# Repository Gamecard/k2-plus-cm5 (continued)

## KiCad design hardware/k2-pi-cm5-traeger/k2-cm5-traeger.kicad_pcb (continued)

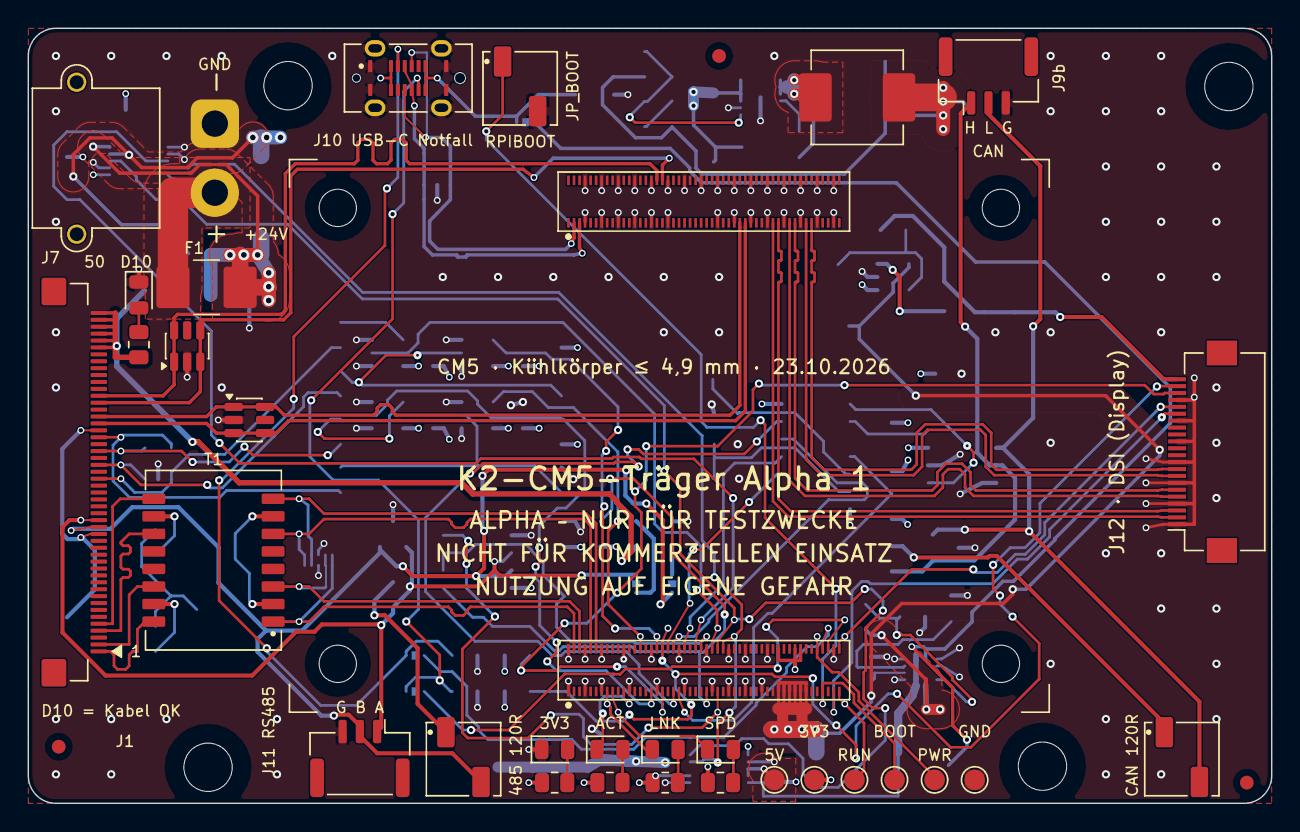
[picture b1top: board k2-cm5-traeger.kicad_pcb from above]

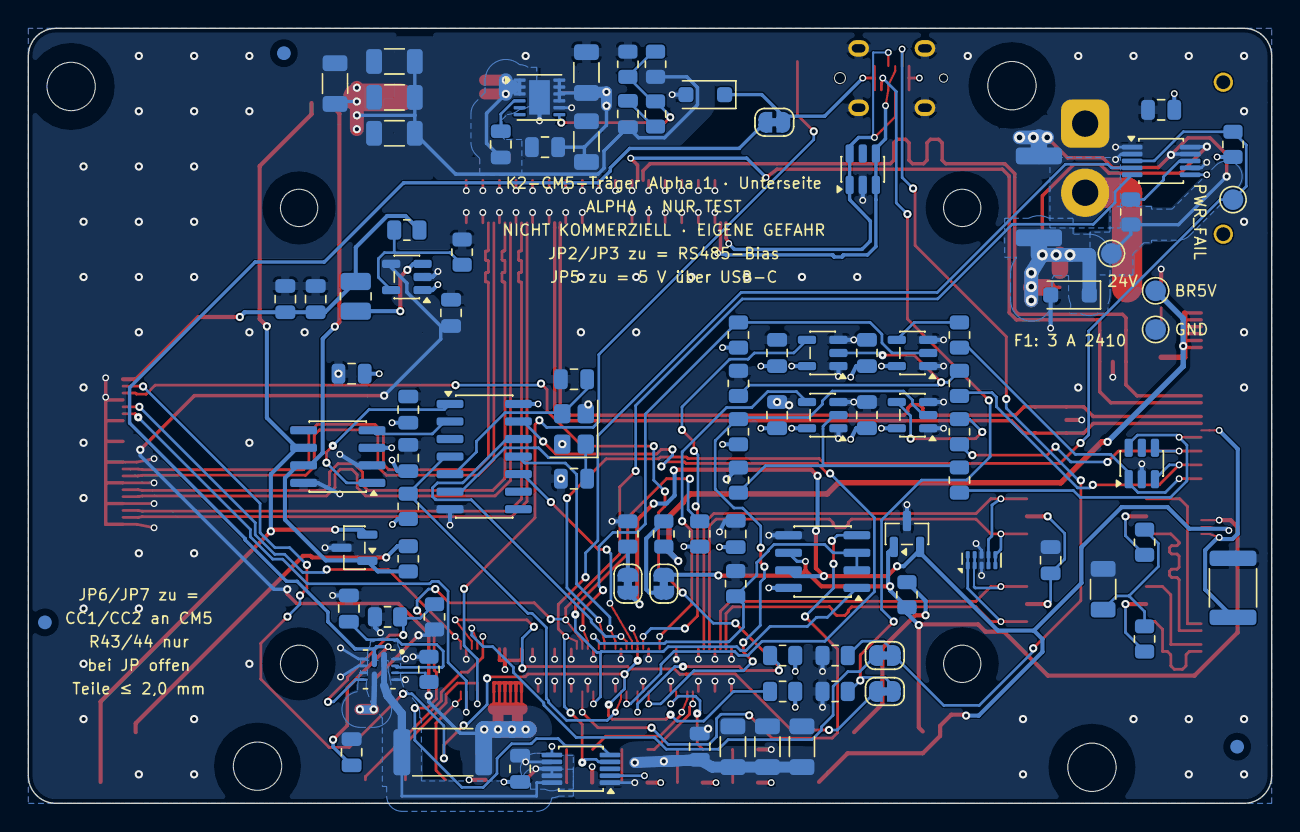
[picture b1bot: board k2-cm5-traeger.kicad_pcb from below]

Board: 4 copper layers, 90.0 x 56.1 mm, 137 parts (99 on the bottom side), 101 nets.

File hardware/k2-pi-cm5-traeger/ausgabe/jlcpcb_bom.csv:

Comment,Designator,Footprint,LCSC Part #,MPN,Manufacturer,Quantity,Notes
22p,"C1,C2",C_0805_2012Metric,C1804,CL21C220JBANNNC,Samsung Electro-Mechanics,2,"Basic; UNTERSEITE: C1,C2"
100n,"C3,C5,C6,C7,C11,C12,C22,C25,C27,C30,C31,C32,C33",C_0805_2012Metric,C49678,CC0805KRX7R9BB104,YAGEO,13,"Basic; UNTERSEITE: C3,C5,C6,C7,C11,C12,C22,C25,C27,C30,C31,C32,C33"
10u,"C4,C18,C34",C_0805_2012Metric,C15850,CL21A106KAYNNNE,Samsung Electro-Mechanics,3,"Basic; UNTERSEITE: C4,C18,C34"
22n,C8,C_0805_2012Metric,C107147,CC0805KRX7R9BB223,YAGEO,1,Extended; UNTERSEITE: C8
10u50,"C9,C10",C_1206_3216Metric,C13585,CL31A106KBHNNNE,Samsung Electro-Mechanics,2,"Basic; UNTERSEITE: C9,C10"
33p,C13,C_0805_2012Metric,C107115,CC0805JRNPO9BN330,YAGEO,1,Extended; UNTERSEITE: C13
22u25,"C14,C15,C16,C17,C19,C20,C21",C_1206_3216Metric,C12891,CL31A226KAHNNNE,Samsung Electro-Mechanics,7,"Basic; UNTERSEITE: C14,C15,C16,C17,C19,C20,C21"
1n2kV,C28,C_1206_3216Metric,C9196,1206B102K202NT,FH (Guangdong Fenghua),1,Basic; UNTERSEITE: C28
22u6,"C35,C36",C_0805_2012Metric,C5674,CL21A226MQQNNNE,Samsung Electro-Mechanics,2,"Extended; UNTERSEITE: C35,C36"
USBLC6-2SC6,"D1,D2,D3",SOT-23-6,C7519,USBLC6-2SC6,STMicroelectronics,3,Extended; Pin 1/Drehung in der JLC-Vorschau prüfen; UNTERSEITE: D3
SRV05-4,D4,SOT-23-6,C5240367,SRV05-4,TWGMC,1,Extended; Pin 1/Drehung in der JLC-Vorschau prüfen; UNTERSEITE: D4
SM712,D5,SOT-23,C502564,SM712,MDD (Microdiode),1,Extended; Pin 1/Drehung in der JLC-Vorschau prüfen; UNTERSEITE: D5
NUP2105L,D6,SOT-23,C14486,NUP2105LT1G,onsemi,1,Extended; Pin 1/Drehung in der JLC-Vorschau prüfen; UNTERSEITE: D6
TPD4E05U06,D7,USON-10_2.5x1.0mm_P0.5mm,C138714,TPD4E05U06DQAR,Texas Instruments,1,Extended; Pin 1/Drehung in der JLC-Vorschau prüfen; UNTERSEITE: D7
SMFJ28A,D8,D_SOD-123F,C5439963,SMFJ28A,BORN,1,Extended; Pin 1/Drehung in der JLC-Vorschau prüfen; UNTERSEITE: D8
LED 0805 rot,D10,LED_0805_2012Metric,C84256,NCD0805R1,Foshan NationStar,1,Basic; Pin 1/Drehung in der JLC-Vorschau prüfen
LED 0805 grün,"D11,D12,D13",LED_0805_2012Metric,C2297,KT-0805G,Hubei KENTO,3,Basic; Pin 1/Drehung in der JLC-Vorschau prüfen
LED 0805 gelb,D14,LED_0805_2012Metric,C2296,KT-0805Y,Hubei KENTO,1,Basic; Pin 1/Drehung in der JLC-Vorschau prüfen
SMF5.0A,D15,D_SOD-123F,C193402,SMF5.0A,MDD (Microdiode),1,Extended; Pin 1/Drehung in der JLC-Vorschau prüfen; UNTERSEITE: D15
3A tauschbar,F1,Sicherungshalter_Littelfuse_157_Nano2_2410,C187520,0157003.DR,Littelfuse,1,Extended
"PTC 0,5A 30V",F3,Fuse_1812_4532Metric,C12559,SMD1812P050TF/30,PTTC (Polytronics),1,Extended; UNTERSEITE: F3
FPC-05FB-50PH20,J1,FFC_XUNPU_FPC-05FB-50PH20_1x50_P0.5mm_Horizontal,C2856838,FPC-05FB-50PH20,XUNPU,1,Extended; Pin 1/Drehung in der JLC-Vorschau prüfen
DF40C-100DS-0.4V(51),"J2A,J2B",CM5_Modul_2xDF40C-100DS-0.4V51_1.5mm,C597931,DF40C-100DS-0.4V(51),Hirose (HRS),2,Extended; Pin 1/Drehung in der JLC-Vorschau prüfen
XT30 24V,J7,AMASS_XT30PW-M_1x02_P2.50mm_Horizontal,C431092,XT30PW-M30.G.Y,Changzhou Amass,1,"Extended; Pin 1/Drehung in der JLC-Vorschau prüfen; THT – Handlöten (hand soldering), Stecköffnung zeigt über Kante A nach außen"
CAN H/L/GND,J9b,JST_GH_BM03B-GHS-TBT_1x03-1MP_P1.25mm_Vertical,C161691,BM03B-GHS-TBT(LF)(SN),JST,1,Extended; Pin 1/Drehung in der JLC-Vorschau prüfen
USB-C stehend,J10,USB_C_Buchse_stehend_16P_TYPE-C-16P-LTH6.8,C5187468,TYPE-C 16P LTH6.8,SHOU HAN,1,Extended; Pin 1/Drehung in der JLC-Vorschau prüfen
RS485 A/B/GND,J11,JST_GH_BM03B-GHS-TBT_1x03-1MP_P1.25mm_Vertical,C161691,BM03B-GHS-TBT(LF)(SN),JST,1,Extended; Pin 1/Drehung in der JLC-Vorschau prüfen
DSI 22-pol.,J12,Hirose_FH12-22S-0.5SH_1x22-1MP_P0.50mm_Horizontal,C597981,FH12-22S-0.5SH(55),Hirose (HRS),1,Extended; Pin 1/Drehung in der JLC-Vorschau prüfen
485 120R,JP_485_TERM,Stiftleiste_1x2_P2.54mm_SMD_stehend,C41417359,HX PZ2.54-1x2P TP-YQ,HX (Hanxia),1,Extended; Pin 1/Drehung in der JLC-Vorschau prüfen
RPIBOOT,JP_BOOT,Stiftleiste_1x2_P2.54mm_SMD_stehend,C41417359,HX PZ2.54-1x2P TP-YQ,HX (Hanxia),1,Extended; Pin 1/Drehung in der JLC-Vorschau prüfen
CAN 120R,JP_CAN_TERM,Stiftleiste_1x2_P2.54mm_SMD_stehend,C41417359,HX PZ2.54-1x2P TP-YQ,HX (Hanxia),1,Extended; Pin 1/Drehung in der JLC-Vorschau prüfen
"4,7µH",L1,L_Changjiang_FXL0630,C167220,FXL0630-4R7-M,cjiang (Changjiang Microelectronics),1,Extended
"2,2µH",L2,L_1008_2520Metric,C97031,WPN252010H2R2MT,lt. LCSC C97031,1,Extended; UNTERSEITE: L2
1k,"R1,R2,R3,R4,R15,R16,R20,R28,R41,R42",R_0805_2012Metric,C17513,0805W8F1001T5E,UNI-ROYAL,10,"Basic; UNTERSEITE: R1,R2,R3,R4,R15,R16,R20,R28"
100k,"R9,R10,R45",R_0805_2012Metric,C149504,0805W8F1003T5E,UNI-ROYAL,3,"Basic; UNTERSEITE: R9,R10,R45"
10k,"R11,R12,R13,R14,R18,R30,R50",R_0805_2012Metric,C17414,0805W8F1002T5E,UNI-ROYAL,7,"Basic; UNTERSEITE: R11,R12,R13,R14,R18,R30,R50"
120,"R17,R19",R_0805_2012Metric,C17437,0805W8F1200T5E,UNI-ROYAL,2,"Basic; UNTERSEITE: R17,R19"
5m,R23,R_2512_6332Metric,C185817,RLM25FEER005,Ralec,1,Extended; UNTERSEITE: R23
10m,R24,R_2512_6332Metric,C2962784,HoLLR2512-2W-10mR-1%,Hongtai,1,Extended; UNTERSEITE: R24
105k,R26,R_0805_2012Metric,C17410,0805W8F1053T5E,UNI-ROYAL,1,Extended; UNTERSEITE: R26
19k1,R27,R_0805_2012Metric,C17508,0805W8F1912T5E,UNI-ROYAL,1,Extended; UNTERSEITE: R27
33k,R29,R_0805_2012Metric,C17633,0805W8F3302T5E,UNI-ROYAL,1,Basic; UNTERSEITE: R29
18k7,R31,R_0805_2012Metric,C17499,0805W8F1872T5E,UNI-ROYAL,1,Extended; UNTERSEITE: R31
75,"R36,R37",R_0805_2012Metric,C17820,0805W8F750JT5E,UNI-ROYAL,2,"Extended; UNTERSEITE: R36,R37"
2k2,"R38,R48,R49",R_0805_2012Metric,C17520,0805W8F2201T5E,UNI-ROYAL,3,"Basic; UNTERSEITE: R48,R49"
470,"R39,R40",R_0805_2012Metric,C17710,0805W8F4700T5E,UNI-ROYAL,2,Basic
22k,R46,R_0805_2012Metric,C17560,0805W8F2202T5E,UNI-ROYAL,1,Basic; UNTERSEITE: R46
H1102NLT,T1,Uebertrager_SMD_H1102NLT_12.7x7.1mm,C18584,H1102NLT,Pulse Electronics,1,Extended; Pin 1/Drehung in der JLC-Vorschau prüfen
MCP2518FD,U1,SOIC-14_3.9x8.7mm_P1.27mm,C626759,MCP2518FDT-H/SL,Microchip,1,Extended; Pin 1/Drehung in der JLC-Vorschau prüfen; UNTERSEITE: U1
SN65HVD230,U2,SOIC-8_3.9x4.9mm_P1.27mm,C12084,SN65HVD230DR,Texas Instruments,1,Extended; Pin 1/Drehung in der JLC-Vorschau prüfen; UNTERSEITE: U2
THVD1450DR,U3,SOIC-8_3.9x4.9mm_P1.27mm,C2671361,THVD1450DR,Texas Instruments,1,Extended; Pin 1/Drehung in der JLC-Vorschau prüfen; UNTERSEITE: U3
INA226,"U4,U5",MSOP-10_3x3mm_P0.5mm,C49851,INA226AIDGSR,Texas Instruments,2,"Extended; Pin 1/Drehung in der JLC-Vorschau prüfen; UNTERSEITE: U4,U5"
LMR51450SDRRR,U7,WSON-12-1EP_3x3mm_P0.5mm_EP1.5x2.5mm,C6890985,LMR51450SDRRR,Texas Instruments,1,Extended; Pin 1/Drehung in der JLC-Vorschau prüfen; UNTERSEITE: U7
TPS2121RUXR,U8,Texas_RUX_VQFN-HR-12_2x2.5mm_P0.5mm,C485916,TPS2121RUXR,Texas Instruments,1,Extended; Pin 1/Drehung in der JLC-Vorschau prüfen; UNTERSEITE: U8
SN74LVC1G125,"U10,U11,U12,U13",SOT-23-5,C23654,SN74LVC1G125DBVR,Texas Instruments,4,"Extended; Pin 1/Drehung in der JLC-Vorschau prüfen; UNTERSEITE: U10,U11,U12,U13"
TLV62569DBVR,U14,SOT-23-5,C141836,TLV62569DBVR,Texas Instruments,1,Extended; Pin 1/Drehung in der JLC-Vorschau prüfen; UNTERSEITE: U14
40 MHz,Y1,Crystal_SMD_3225-4Pin_3.2x2.5mm,C426990,S3240000151040,JGHC,1,Extended; Pin 1/Drehung in der JLC-Vorschau prüfen; UNTERSEITE: Y1

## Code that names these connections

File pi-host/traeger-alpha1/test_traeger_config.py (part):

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    keine GPIO-Doppelbelegung (Overlays + Stromausfall-Dienst); nur unbeschaltete Pins
    dürfen nebenbei belegt werden (GPIO16 CTS, GPIO7 CE1).
 3. GPIO6 und GPIO26 (früher Toolhead-eFuse) werden nirgends verwendet; im Schaltplan frei.
 4. CAN: spi0-0 = CAN_CS an GPIO8, interrupt=25 = CAN_INT, oscillator = Quarz Y1.
 5. RS485: THVD1450 DE und ~RE an RS485_DE = GPIO17 = UART0-RTS (uart0-pi5,rs485).
 6. INA226-Overlay: Adressen aus A1/A0, Shunts aus Generator + Stückliste, ALERT 0x40 ->
    PWR_FAIL_N -> GPIO27 = k2_stromausfall-Standard; kein 0x44 mehr.
 7. DSI: vc4-kms-dsi-7inch (DSI1) <-> MIPI1-Netze, I2C ID_SD/ID_SC = GPIO0/1.
 8. Klipper-Ausschnitte: ttyAMA<n> passt zu uart<n>-pi5; Main = UART4, Düse = UART2
    (Generator), RS485 = ttyAMA0 mit rs485_de: kernel (von k2_485.py akzeptiert),
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    1: ("DSI_SCL", "i2c_csi_dsi SCL (Display)", "vc4-kms-dsi-7inch"),
    2: ("I2C1_SDA", "I2C1 SDA (INA226)", "i2c_arm"),
    3: ("I2C1_SCL", "I2C1 SCL (INA226)", "i2c_arm"),
    4: ("UART2_TX", "UART2 TX (Düsen-MCU)", "uart2-pi5"),
    5: ("UART2_RX", "UART2 RX (Düsen-MCU)", "uart2-pi5"),
    7: (None, "SPI0 CE1 (unbenutzt, nicht beschaltet)", "mcp251xfd"),
    8: ("CAN_CS", "SPI0 CE0 (MCP2518FD)", "mcp251xfd"),
    9: ("CAN_MISO", "SPI0 MISO", "mcp251xfd"),
    10: ("CAN_MOSI", "SPI0 MOSI", "mcp251xfd"),
    11: ("CAN_SCK", "SPI0 SCLK", "mcp251xfd"),
    12: ("UART4_TX", "UART4 TX (Main-MCU)", "uart4-pi5"),
    13: ("UART4_RX", "UART4 RX (Main-MCU)", "uart4-pi5"),
    14: ("UART0_TX", "UART0 TX (RS485 DI)", "uart0-pi5"),
    15: ("UART0_RX", "UART0 RX (RS485 RO)", "uart0-pi5"),
    16: (None, "UART0 CTS (durch rs485 belegt, nicht beschaltet)", "uart0-pi5"),
    17: ("RS485_DE", "UART0 RTS = DE/~RE THVD1450", "uart0-pi5"),
    25: ("CAN_INT", "MCP2518FD nINT", "mcp251xfd"),
    27: ("PWR_FAIL_N", "INA226 0x40 ALERT (Stromausfall)", "k2_stromausfall"),
}
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            belegt.setdefault(gpio, []).append("%s (%s)" % (funk, schl))
    kfg_sa = re.search(r"^K2SA_GPIO_OFFSET=(\d+)", lies(os.path.join(HIER, "k2_stromausfall.default")), re.M)
    sa_gpio = int(kfg_sa.group(1))
    belegt.setdefault(sa_gpio, []).append("PWR_FAIL_N-Eingang (k2_stromausfall)")
    doppelt = {g: v for g, v in belegt.items() if len(v) > 1}
    check("GPIO: keine Doppelbelegung", not doppelt, str(doppelt))
    check("GPIO: belegte Pins = SOLL-Tabelle", set(belegt) == set(SOLL),
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    check("RS485: uart0-pi5 mit rs485 (Kernel-DE über RTS)", params["uart0-pi5"].get("rs485") is True)
    check("RS485: keine invertierte RTS-Polarität (THVD1450 DE aktiv high)",
          "rs485_invert_rts" not in params["uart0-pi5"])
    check("UART2/UART4 ohne ctsrts (würde GPIO6/7 bzw. GPIO14/15 belegen)",
          not params["uart2-pi5"] and not params["uart4-pi5"])
    check("config.txt: force_eeprom_read=0 (kein HAT-EEPROM, ID_SD/SC = Display-I2C)",
          "force_eeprom_read=0" in zeilen)
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    check("CAN: oscillator = Quarz Y1", m and int(p["oscillator"]) == int(m.group(1)) * 1000000,
          "%s / %s" % (p.get("oscillator"), m and m.group(1)))
    u1 = teil_pins(src, "U1")
    check("CAN: MCP2518FD nINT (Pin 4) = CAN_INT, nCS (13) = CAN_CS, OSC an Y1",
          u1.get("4") == "CAN_INT" and u1.get("13") == "CAN_CS"
          and {u1.get("5"), u1.get("6")} == {y1.get("1"), y1.get("3")}, str(u1))
    check("CAN: SDI(11)=MOSI, SDO(12)=MISO, SCK(10)",
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        check("Overlay: compatible ti,ina226 (0x%02x)" % reg, 'compatible = "ti,ina226"' in inhalt)
        ov[reg] = shunt
    check("Overlay: genau 0x40 und 0x41", sorted(ov) == [0x40, 0x41], str(ov))
    # Adressen aus A1 (Pin 1) / A0 (Pin 2): GND=0, VS(CM5_3V3)=1 (SDA/SCL hier nicht verwendet)
    wert = {"GND": 0, "CM5_3V3": 1}
    gefunden = {}
    for ref in ("U4", "U5", "U6"):
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    check("Schaltplan: INA226 U4 = 0x40, U5 = 0x41, kein U6/0x44",
          gefunden == {"U4": 0x40, "U5": 0x41}, str(gefunden))
    u4, u5 = teil_pins(src, "U4"), teil_pins(src, "U5")
    check("Schaltplan: U4 ALERT (Pin 3) = PWR_FAIL_N", u4.get("3") == "PWR_FAIL_N")
    sp, _ = schaltplan_gpio(werte)
    check("Schaltplan: PWR_FAIL_N an GPIO27 (k2_stromausfall-Standard)",
          sp.get(27, (None,))[0] == "PWR_FAIL_N")
    r50 = widerstand(src, "R50")
    check("Schaltplan: R50 Pull-up PWR_FAIL_N nach CM5_3V3", r50 and set(r50[1:]) == {"CM5_3V3", "PWR_FAIL_N"}, str(r50))
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        check("Stückliste: R23 5m, R24 10m",
              zeilen.get("R23", [None, None])[1] == "5m" and zeilen.get("R24", [None, None])[1] == "10m")
    sa = lies(os.path.join(HIER, "k2_stromausfall.py"))
    check("k2_stromausfall: Standard 0x40, I2C1, GPIO27, 20 V",
          '"K2SA_INA_ADR": "0x40"' in sa and '"K2SA_I2C_BUS": "1"' in sa
          and '"K2SA_GPIO_NAME": "GPIO27"' in sa and '"K2SA_GRENZE_MV": "20000"' in sa)


def test_dsi(src, werte):
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          {"DSI1_C_P", "DSI1_C_N", "DSI1_D0_P", "DSI1_D0_N", "DSI1_D1_P", "DSI1_D1_N"} <= netze)
    m = re.search(r"\n\s*j12 = \{(.*?)\}", src, re.S)
    j12 = dict(re.findall(r'"(\d+)":\s*"([^"]*)"', m.group(1))) if m else teil_pins(src, "J12")
    check("DSI: J12 SCL/SDA = DSI_SCL/DSI_SDA (Pin 20/21)",
          j12 and j12.get("20") == "DSI_SCL" and j12.get("21") == "DSI_SDA", str(j12))


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
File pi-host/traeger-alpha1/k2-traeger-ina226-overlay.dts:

// K2-CM5-Traeger Alpha 1: INA226-Strommesser an I2C1 (GPIO2 SDA / GPIO3 SCL)
// als hwmon (Treiber ina2xx). Erzeugen auf dem Pi (macht install-traeger.sh):
//   dtc -@ -I dts -O dtb -o /boot/firmware/overlays/k2-traeger-ina226.dtbo \
//       k2-traeger-ina226-overlay.dts
// Laden: dtoverlay=k2-traeger-ina226 (config.txt)
//
// Adressen laut Schaltplan (generator/k2_traeger.py, INA226 A1/A0):
//   U4 0x40: A1 = A0 = GND, Shunt R23 5 mOhm, misst 24-V-Eingang (hinter F1),
//            ALERT -> PWR_FAIL_N -> GPIO27 (Stromausfall, k2_stromausfall)
//   U5 0x41: A1 = GND, A0 = VS, Shunt R24 10 mOhm, misst CM5-5V
// shunt-resistor in Mikroohm (Bindung ti,ina2xx.yaml). Der Treiber setzt beim
// Laden ALERT-Latch EIN (ina2xx.c, ina2xx_init) - k2_stromausfall rechnet damit.
// Ein INA226 0x44 (Toolhead) gibt es seit dem Umbau 24.10.2026 nicht mehr.

/dts-v1/;
/plugin/;

/ {
	compatible = "brcm,bcm2712";

	fragment@0 {
		target = <&i2c_arm>;
		__overlay__ {
			#address-cells = <1>;
			#size-cells = <0>;
			status = "okay";

			k2_ina_eingang: ina226@40 {
				compatible = "ti,ina226";
				reg = <0x40>;
				shunt-resistor = <5000>;
				label = "k2_eingang_24v";
				status = "okay";
			};

			k2_ina_cm5: ina226@41 {
				compatible = "ti,ina226";
				reg = <0x41>;
				shunt-resistor = <10000>;
				label = "k2_cm5_5v";
				status = "okay";
			};
		};
	};

	__overrides__ {
		// z. B. dtoverlay=k2-traeger-ina226,shunt40=5000
		shunt40 = <&k2_ina_eingang>,"shunt-resistor:0";
		shunt41 = <&k2_ina_cm5>,"shunt-resistor:0";
		ina41 = <&k2_ina_cm5>,"status";
	};
};
